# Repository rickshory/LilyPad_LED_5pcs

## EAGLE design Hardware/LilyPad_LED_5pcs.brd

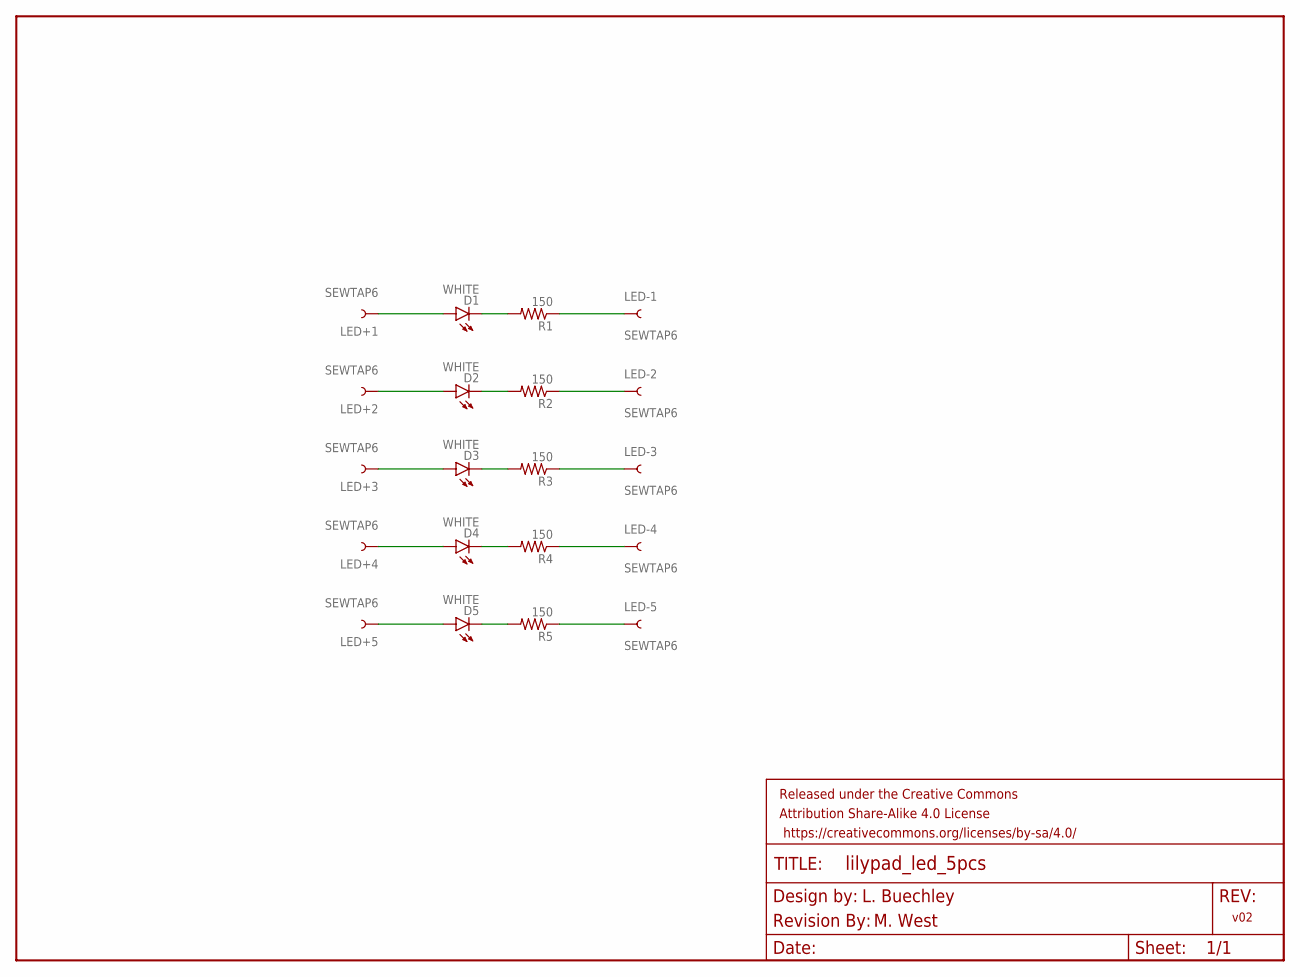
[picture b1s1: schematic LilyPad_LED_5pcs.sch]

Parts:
D1, D2, D3, D4, D5: WHITE; LED-1206
FRAME1: FRAME-LETTER; CREATIVE_COMMONS
LED+1, LED+2, LED+3, LED+4, LED+5: SEWTAP6; PETAL-SMALL-2SIDE
LED-1, LED-2, LED-3, LED-4, LED-5: SEWTAP6; PETAL-SMALL-2SIDE
R1, R2, R3, R4, R5: 150; 0603-RES
U$6: REVISION

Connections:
1: D1.A, LED+1.1
2: D1.C, R1.2
3: LED-1.1, R1.1
4: D2.A, LED+2.1
5: D2.C, R2.2
6: LED-2.1, R2.1
7: D3.A, LED+3.1
8: D3.C, R3.2
9: LED-3.1, R3.1
10: D4.A, LED+4.1
11: D4.C, R4.2
12: LED-4.1, R4.1
13: D5.A, LED+5.1
14: D5.C, R5.2
15: LED-5.1, R5.1

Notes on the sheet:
M. West
L. Buechley
v02

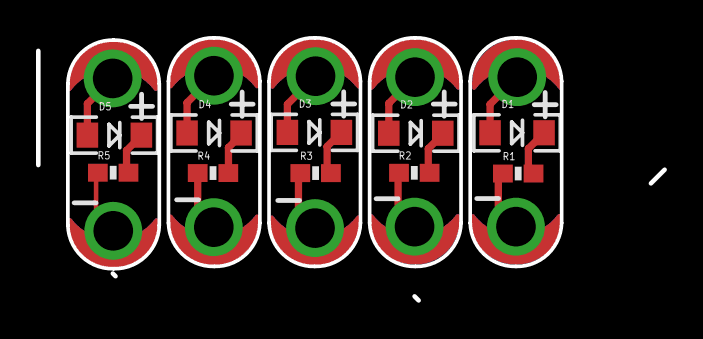
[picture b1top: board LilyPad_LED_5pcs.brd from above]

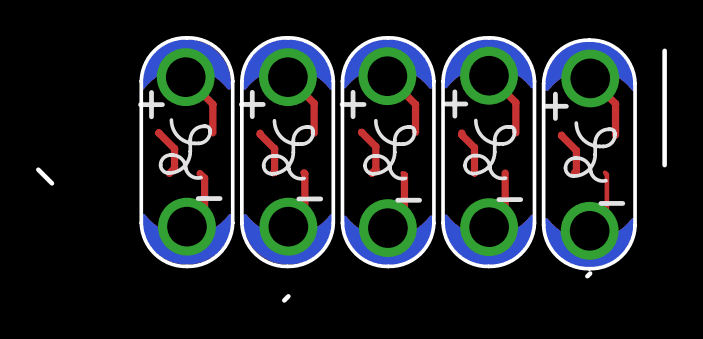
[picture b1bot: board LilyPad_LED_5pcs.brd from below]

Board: 2 copper layers, 34.8 x 14.6 mm, 27 parts (5 on the bottom side), 15 nets.

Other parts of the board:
U$1, U$2, U$3, U$4, U$5: LOGO-L

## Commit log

2016-04-19 Updated files
2016-04-25 updated brd and sch files
2016-04-25 Updated Brd File
2016-04-26 Updated brd file per QC
2016-06-07 Updated Brd files -- Chnaged orientation of LilyPad logo and cleaned up the centering a bit
2016-06-07 Updated board files
2016-06-16 Updated Brd File per Eng Design Rev
2016-06-21 created panel v10
2016-10-14 Updating README with product links

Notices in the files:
parts and their libraries:
SparkFun-LED: Licensing: Creative Commons ShareAlike 4.0 International - https://creativecommons.org/licenses/by-sa/4.0
SparkFun-Aesthetics: Released under the Creative Commons Attribution Share-Alike 4.0 License
SparkFun-Aesthetics: https://creativecommons.org/licenses/by-sa/4.0
